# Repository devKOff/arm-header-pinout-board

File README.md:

# ARM Header Pinout Board

A custom breakout and header pinout board designed for ARM microcontroller development, providing structured signal routing, power distribution, and debugging access points.

## 📋 Project Overview

The **ARM Header Pinout Board** is engineered to simplify prototyping and peripheral interfacing for ARM-based microcontrollers. It breaks out all core GPIO, communication buses (SPI, I2C, UART), and power rails into clean, labeled standard pin headers, minimizing wiring clutter on the breadboard.

---

## 📂 Repository Structure

```text
arm-header-pinout-board/
├── .history/           # Automatic local schematic and PCB version backups
├── Block 6 — Crystal/  # Sub-schematic blocks or modular design files
├── bom/                # Bill of Materials (CSV / HTML)
├── docs/               # Datasheets, schematics PDFs, and pinout diagrams
├── gerbers/            # Production-ready Gerber and drill files for PCB fabrication
├── hardware/           # 3D step models, enclosure designs, or mechanical CAD files
├── images/             # Photos, renders, and wiring diagrams
├── .gitignore          # Git exclusion rules for KiCad temporary/lock files
├── LICENSE             # Open-source license governing the hardware/code
├── README.md           # Project documentation
├── changelog.md        # Version history and revision notes
├── project_3.kicad_pro # KiCad project master file
└── project_3.kicad_pcb # Main printed circuit board layout

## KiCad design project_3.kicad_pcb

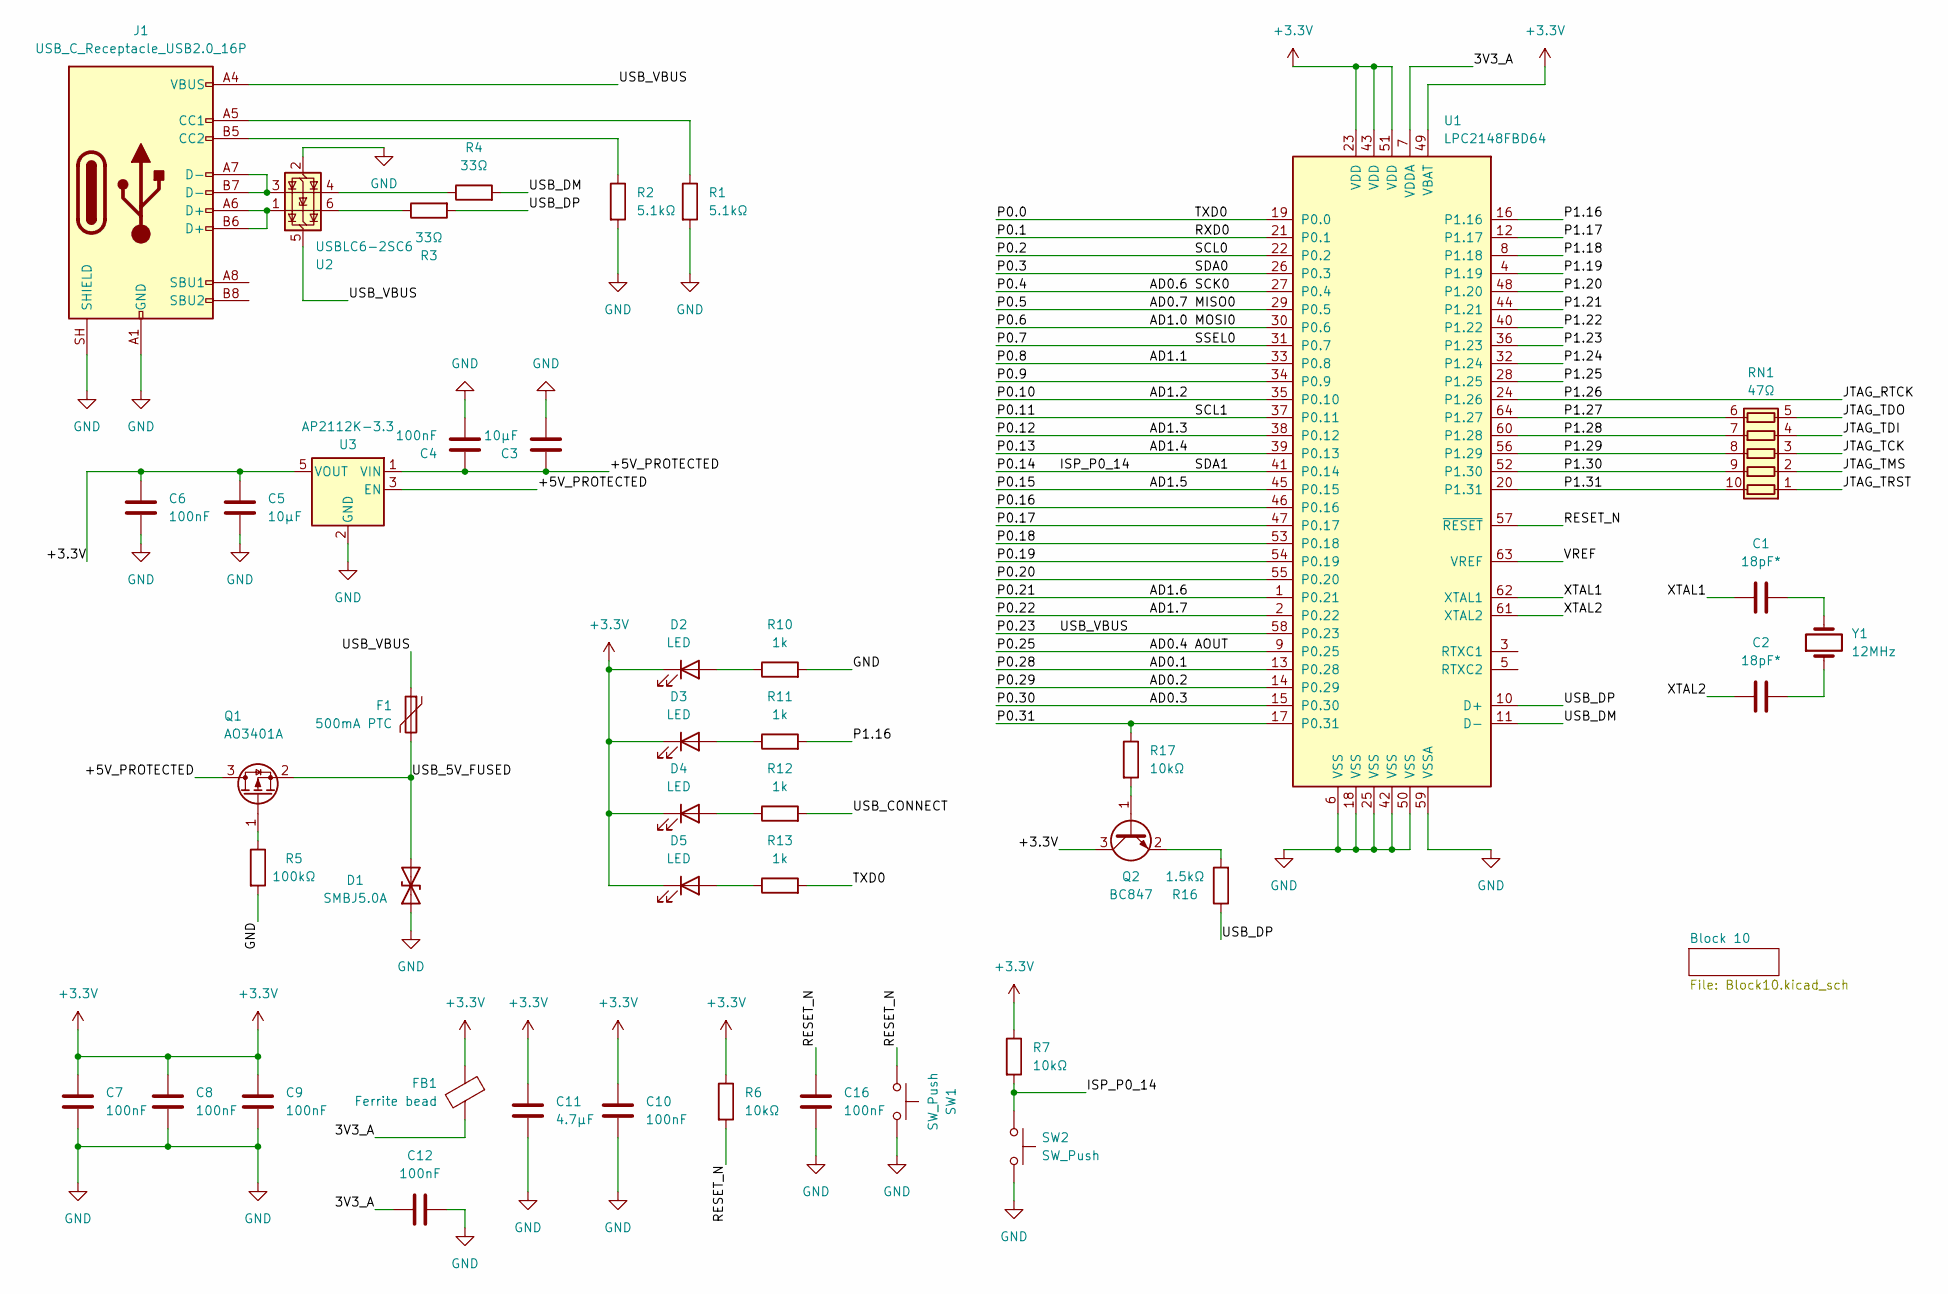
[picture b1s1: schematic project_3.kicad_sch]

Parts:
C1, C2: 18pF*; R_0603_1608Metric
C3, C5: 10µF; C_0805_2012Metric
C4, C6, C7, C8, C9, C10, C12, C16: 100nF; C_0603_1608Metric
C11: 4.7µF; C_0603_1608Metric
D1: SMBJ5.0A; D_SMA
D2, D3, D4, D5: LED; LED_0603_1608Metric
F1: 500mA PTC; Fuse_1206_3216Metric
FB1: Ferrite bead; L_0603_1608Metric
J1: USB_C_Receptacle_USB2.0_16P; USB_C_Receptacle_GCT_USB4105-xx-A_16P_TopMnt_Horizontal
Q1: AO3401A; SOT-23-5
Q2: BC847; SOT-23
R1, R2: 5.1kΩ; R_0603_1608Metric
R3, R4: 33Ω; R_0603_1608Metric
R5: 100kΩ; R_0603_1608Metric
R6, R7, R17: 10kΩ; R_0603_1608Metric
R10, R11, R12, R13: 1k; R_0603_1608Metric
R16: 1.5kΩ; SOT-23
RN1: 47Ω; R_Array_SIP14
SW1, SW2: SW_Push; SW_SPST_TL3305A
U1: LPC2148FBD64; LQFP-64_10x10mm_P0.5mm
U2: USBLC6-2SC6; SOT-23-6
U3: AP2112K-3.3; SOT-23-5
Y1: 12MHz; Crystal_SMD_3225-4Pin_3.2x2.5mm

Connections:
+3.3V: C5.1, C6.1, C7.1, C8.1, C9.1, C10.1, C11.1, D2.1 (K), D3.1 (K), D4.1 (K), D5.1 (K), FB1.1, Q2.3 (C), R6.1, R7.1, U1.23 (VDD), U1.43 (VDD), U1.49 (VBAT), U1.51 (VDD), U3.5 (VOUT)
/3V3_A: C12.2, FB1.2, U1.7 (VDDA)
/+5V_PROTECTED: C3.1, C4.1, Q1.3 (D), U3.1 (VIN), U3.3 (EN)
/AD0.1: U1.13 (P0.28)
/AD0.2: U1.14 (P0.29)
/AD0.3: U1.15 (P0.30)
/AD0.4: U1.9 (P0.25)
/AD0.6: U1.27 (P0.4)
/AD0.7: U1.29 (P0.5)
/AD1.0: U1.30 (P0.6)
/AD1.1: U1.33 (P0.8)
/AD1.2: U1.35 (P0.10)
/AD1.3: U1.38 (P0.12)
/AD1.4: U1.39 (P0.13)
/AD1.5: U1.45 (P0.15)
/AD1.6: U1.1 (P0.21)
/AD1.7: U1.2 (P0.22)
/ISP_P0_14: R7.2, SW2.1, U1.41 (P0.14)
/JTAG_RTCK: U1.24 (P1.26)
/JTAG_TCK: RN1.3 (R3.1)
/JTAG_TDI: RN1.4 (R4.1)
/JTAG_TDO: RN1.5 (R5.1)
/JTAG_TMS: RN1.2 (R2.1)
/JTAG_TRST: RN1.1 (R1.1)
/P0.0: R13.2, U1.19 (P0.0)
/P0.1: U1.21 (P0.1)
/P0.2: U1.22 (P0.2)
/P0.3: U1.26 (P0.3)
/P0.7: U1.31 (P0.7)
/P0.9: U1.34 (P0.9)
/P0.11: U1.37 (P0.11)
/P0.16: U1.46 (P0.16)
/P0.17: U1.47 (P0.17)
/P0.18: U1.53 (P0.18)
/P0.19: U1.54 (P0.19)
/P0.20: U1.55 (P0.20)
/P0.23: F1.1, J1.A4 (VBUS), J1.A9 (VBUS), J1.B4 (VBUS), J1.B9 (VBUS), U1.58 (P0.23), U2.5 (VBUS)
/P0.31: R17.1, U1.17 (P0.31)
/P1.16: R11.2, U1.16 (P1.16)
/P1.17: U1.12 (P1.17)
/P1.18: U1.8 (P1.18)
/P1.19: U1.4 (P1.19)
/P1.20: U1.48 (P1.20)
/P1.21: U1.44 (P1.21)
/P1.22: U1.40 (P1.22)
/P1.23: U1.36 (P1.23)
/P1.24: U1.32 (P1.24)
/P1.25: U1.28 (P1.25)
/P1.27: RN1.6 (R5.2), U1.64 (P1.27)
/P1.28: RN1.7 (R4.2), U1.60 (P1.28)
/P1.29: RN1.8 (R3.2), U1.56 (P1.29)
/P1.30: RN1.9 (R2.2), U1.52 (P1.30)
/P1.31: RN1.10 (R1.2), U1.20 (P1.31)
/RESET_N: C16.1, R6.2, SW1.2, U1.57 (~RESET)
/USB_5V_FUSED: D1.2 (A2), F1.2, Q1.2 (S)
/USB_CONNECT: R12.2
/USB_DM: R4.2, U1.11 (D-)
/USB_DP: R3.2, R16.1, U1.10 (D+)
/VREF: U1.63 (VREF)
/XTAL1: C1.1, U1.62 (XTAL1)
/XTAL2: C2.1, U1.61 (XTAL2)
GND: C3.2, C4.2, C5.2, C6.2, C7.2, C8.2, C9.2, C10.2, C11.2, C12.1, C16.2, D1.1 (A1), J1.A1 (GND), J1.A12 (GND), J1.B1 (GND), J1.B12 (GND), J1.SH (SHIELD), R1.2, R2.2, R5.2, R10.2, SW1.1, SW2.2, U1.6 (VSS), U1.18 (VSS), U1.25 (VSS), U1.42 (VSS), U1.50 (VSS), U1.59 (VSSA), U2.2 (GND), U3.2 (GND); also elsewhere on the board
unnamed: C1.2, Y1.2
unnamed: C2.2, Y1.1
unnamed: D2.2 (A), R10.1
unnamed: D3.2 (A), R11.1
unnamed: D4.2 (A), R12.1
unnamed: D5.2 (A), R13.1
unnamed: J1.A5 (CC1), R1.1
unnamed: J1.B5 (CC2), R2.1
unnamed: J1.A6 (D+), J1.B6 (D+), U2.1 (I/O1)
unnamed: J1.A7 (D-), J1.B7 (D-), U2.3 (I/O2)
unnamed: Q1.1 (G), R5.1
unnamed: Q2.1 (B), R17.2
unnamed: Q2.2 (E), R16.2
unnamed: R3.1, U2.6 (I/O1)
unnamed: R4.1, U2.4 (I/O2)

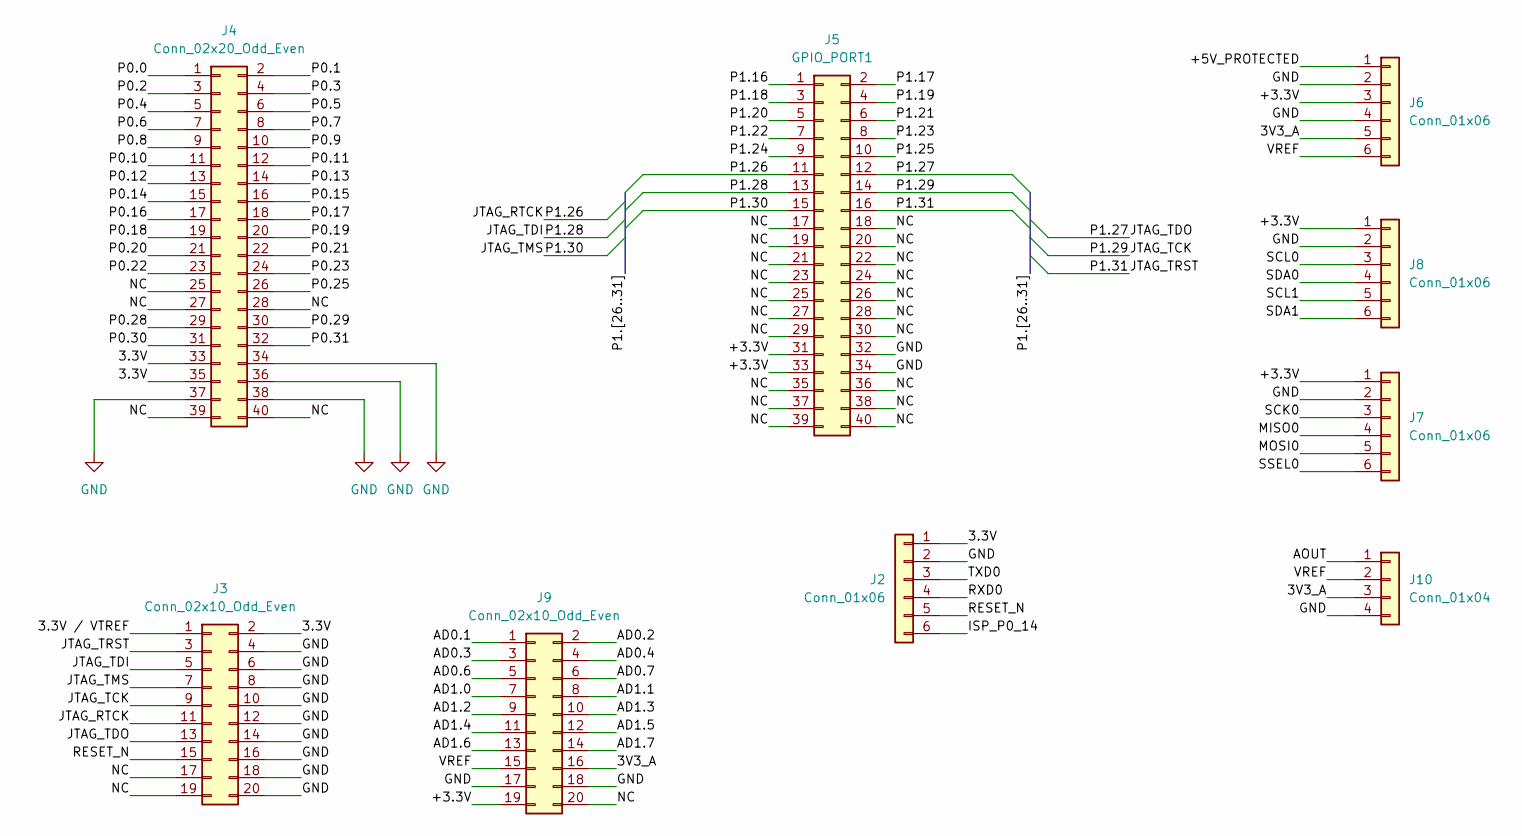
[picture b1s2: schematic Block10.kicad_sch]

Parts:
J2, J6, J7, J8: Conn_01x06; PinHeader_1x06_P2.54mm_Vertical
J3, J9: Conn_02x10_Odd_Even; PinHeader_2x10_P2.54mm_Vertical
J4: Conn_02x20_Odd_Even; PinHeader_2x20_P2.54mm_Vertical
J5: GPIO_PORT1; PinHeader_2x20_P2.54mm_Vertical
J10: Conn_01x04; PinHeader_1x04_P2.54mm_Vertical

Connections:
/Block 10/3.3V: J2.1, J3.2, J4.33, J4.35
/Block 10/3.3V / VTREF: J3.1
/Block 10/3V3_A: J6.5, J9.16, J10.3
/Block 10/+3.3V: J5.31, J5.33, J6.3, J7.1, J8.1, J9.19
/Block 10/+5V_PROTECTED: J6.1
/Block 10/AD0.1: J9.1
/Block 10/AD0.2: J9.2
/Block 10/AD0.3: J9.3
/Block 10/AD0.4: J9.4
/Block 10/AD0.6: J9.5
/Block 10/AD0.7: J9.6
/Block 10/AD1.0: J9.7
/Block 10/AD1.1: J9.8
/Block 10/AD1.2: J9.9
/Block 10/AD1.3: J9.10
/Block 10/AD1.4: J9.11
/Block 10/AD1.5: J9.12
/Block 10/AD1.6: J9.13
/Block 10/AD1.7: J9.14
/Block 10/AOUT: J10.1
/Block 10/ISP_P0_14: J2.6
/Block 10/MISO0: J7.4
/Block 10/MOSI0: J7.5
/Block 10/NC: J3.17, J3.19, J4.25, J4.27, J4.28, J4.39, J4.40, J5.17, J5.18, J5.19, J5.20, J5.21, J5.22, J5.23, J5.24, J5.25, J5.26, J5.27, J5.28, J5.29, J5.30, J5.35, J5.36, J5.37, J5.38, J5.39, J5.40, J9.20
/Block 10/P0.0: J4.1
/Block 10/P0.1: J4.2
/Block 10/P0.2: J4.3
/Block 10/P0.3: J4.4
/Block 10/P0.4: J4.5
/Block 10/P0.5: J4.6
/Block 10/P0.6: J4.7
/Block 10/P0.7: J4.8
/Block 10/P0.8: J4.9
/Block 10/P0.9: J4.10
/Block 10/P0.10: J4.11
/Block 10/P0.11: J4.12
/Block 10/P0.12: J4.13
/Block 10/P0.13: J4.14
/Block 10/P0.14: J4.15
/Block 10/P0.15: J4.16
/Block 10/P0.16: J4.17
/Block 10/P0.17: J4.18
/Block 10/P0.18: J4.19
/Block 10/P0.19: J4.20
/Block 10/P0.20: J4.21
/Block 10/P0.21: J4.22
/Block 10/P0.22: J4.23
/Block 10/P0.23: J4.24
/Block 10/P0.25: J4.26
/Block 10/P0.28: J4.29
/Block 10/P0.29: J4.30
/Block 10/P0.30: J4.31
/Block 10/P0.31: J4.32
/Block 10/P1.16: J5.1
/Block 10/P1.17: J5.2
/Block 10/P1.18: J5.3
/Block 10/P1.19: J5.4
/Block 10/P1.20: J5.5
/Block 10/P1.21: J5.6
/Block 10/P1.22: J5.7
/Block 10/P1.23: J5.8
/Block 10/P1.24: J5.9
/Block 10/P1.25: J5.10
/Block 10/P1.26: J3.11, J5.11
/Block 10/P1.27: J3.13, J5.12
/Block 10/P1.28: J3.5, J5.13
/Block 10/P1.29: J3.9, J5.14
/Block 10/P1.30: J3.7, J5.15
/Block 10/P1.31: J3.3, J5.16
/Block 10/RESET_N: J2.5, J3.15
/Block 10/RXD0: J2.4
/Block 10/SCK0: J7.3
/Block 10/SCL0: J8.3
/Block 10/SCL1: J8.5
/Block 10/SDA0: J8.4
/Block 10/SDA1: J8.6
/Block 10/SSEL0: J7.6
/Block 10/TXD0: J2.3
/Block 10/VREF: J6.6, J9.15, J10.2
GND: J2.2, J3.4, J3.6, J3.8, J3.10, J3.12, J3.14, J3.16, J3.18, J3.20, J4.34, J4.36, J4.37, J4.38, J5.32, J5.34, J6.2, J6.4, J7.2, J8.2, J9.17, J9.18, J10.4; also elsewhere on the board

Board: 2 copper layers, 52 parts (0 on the bottom side), 47 nets, no tracks yet.
